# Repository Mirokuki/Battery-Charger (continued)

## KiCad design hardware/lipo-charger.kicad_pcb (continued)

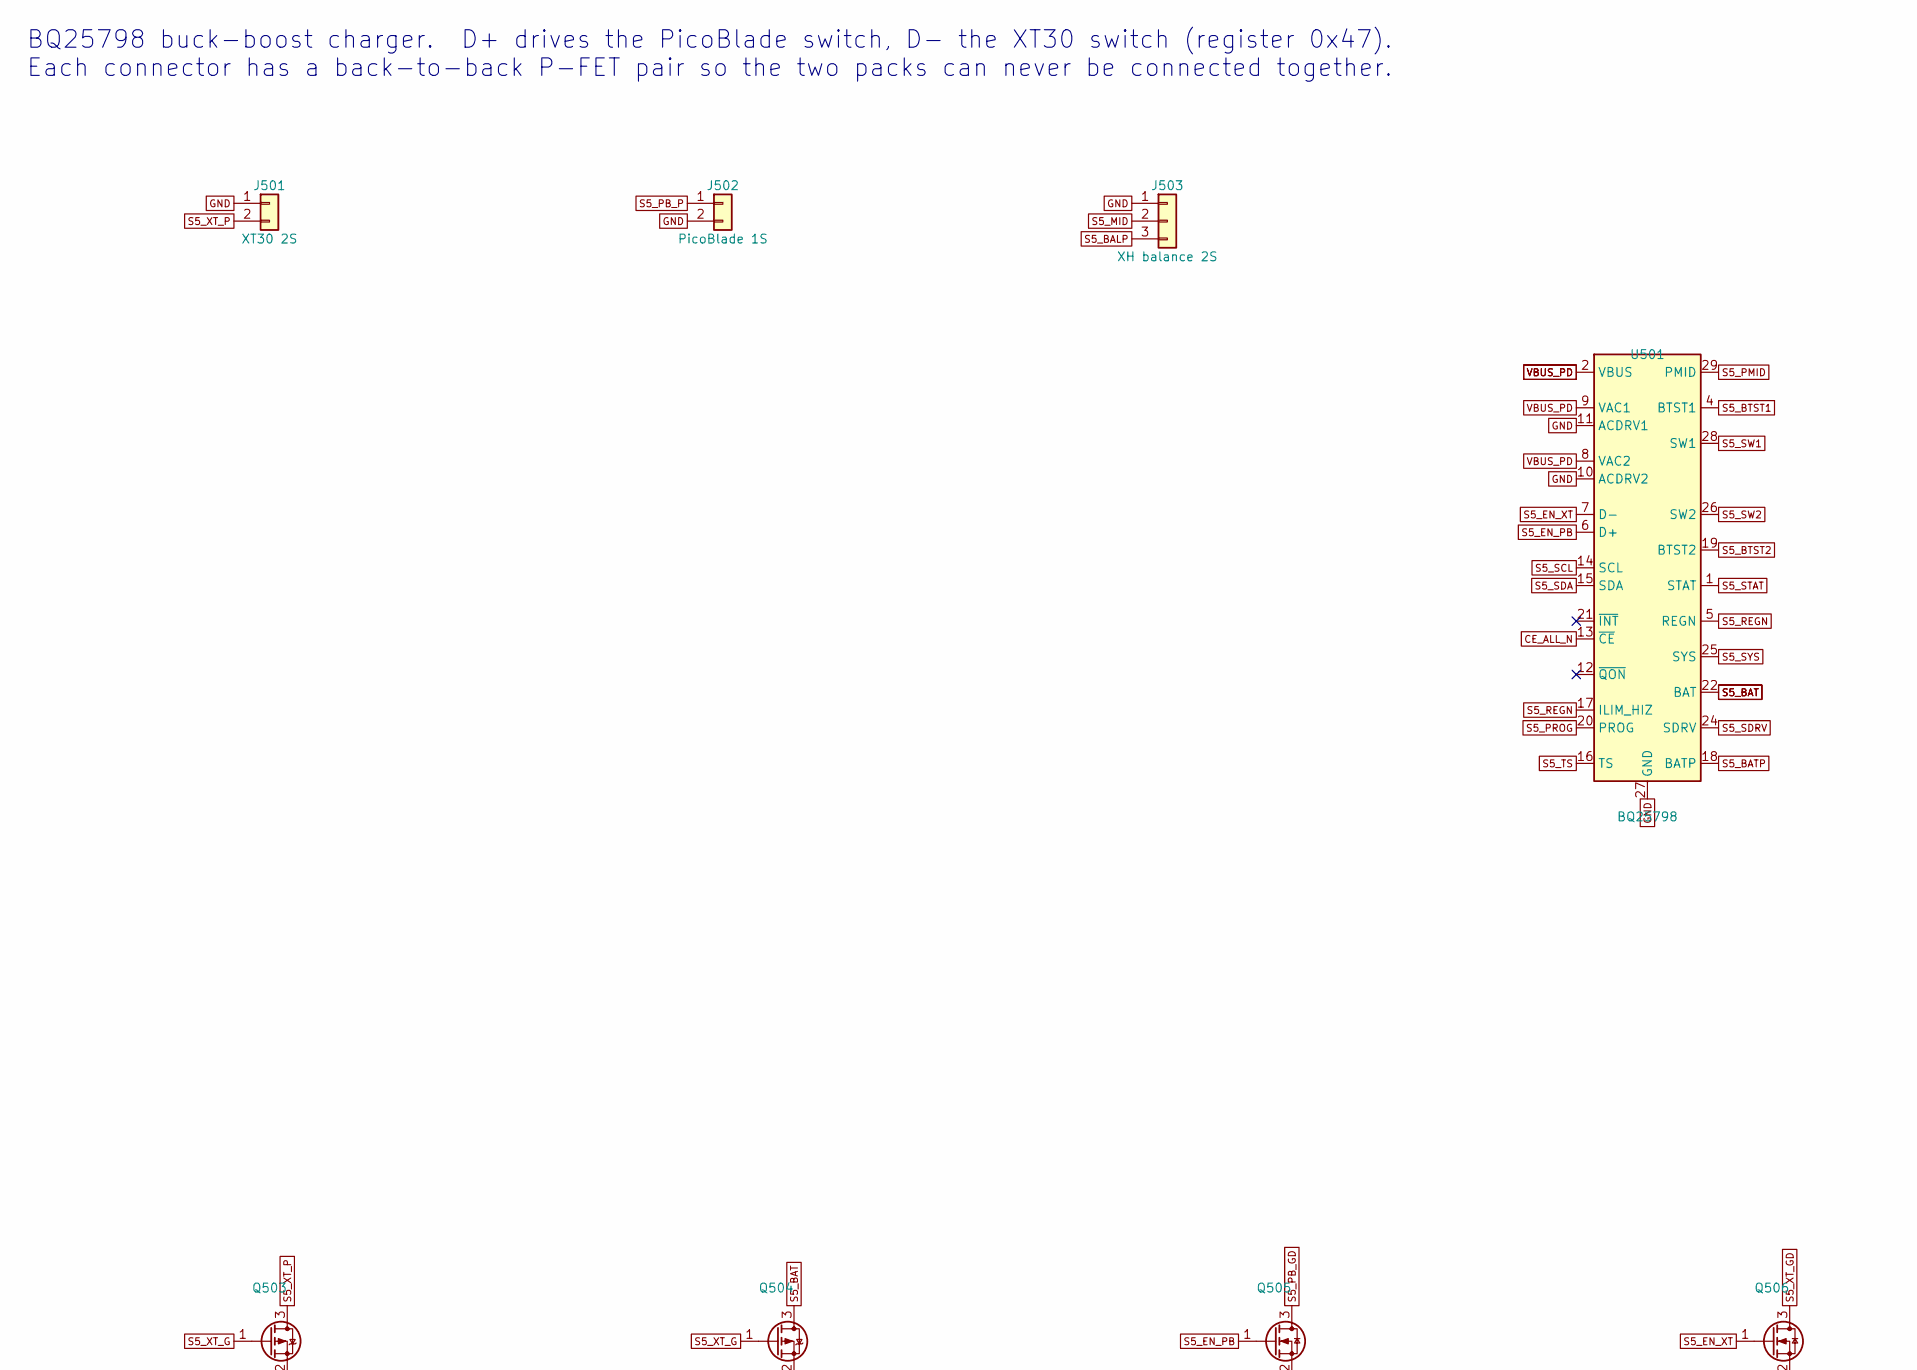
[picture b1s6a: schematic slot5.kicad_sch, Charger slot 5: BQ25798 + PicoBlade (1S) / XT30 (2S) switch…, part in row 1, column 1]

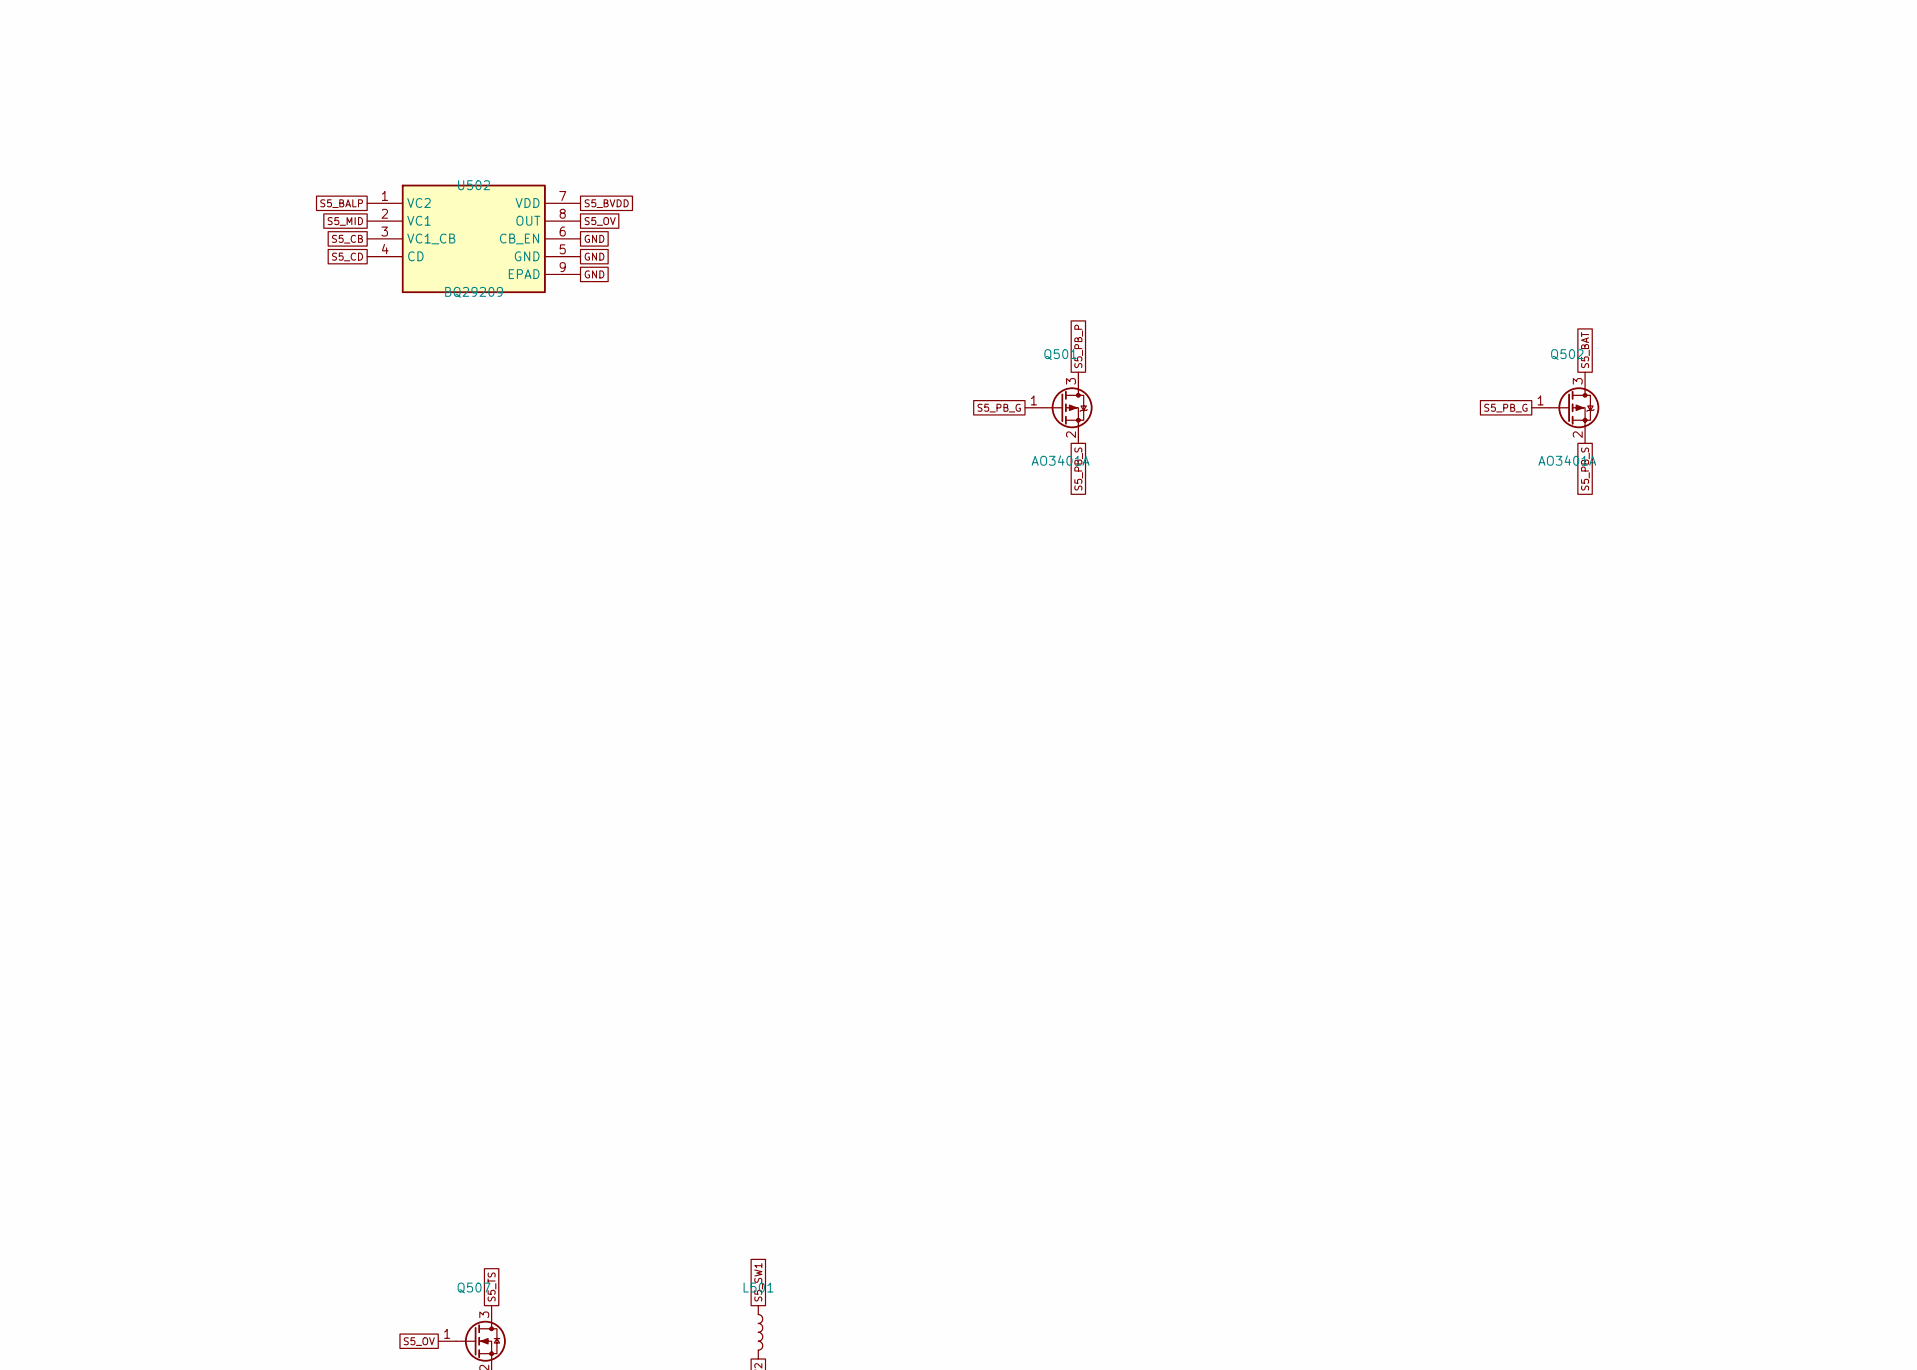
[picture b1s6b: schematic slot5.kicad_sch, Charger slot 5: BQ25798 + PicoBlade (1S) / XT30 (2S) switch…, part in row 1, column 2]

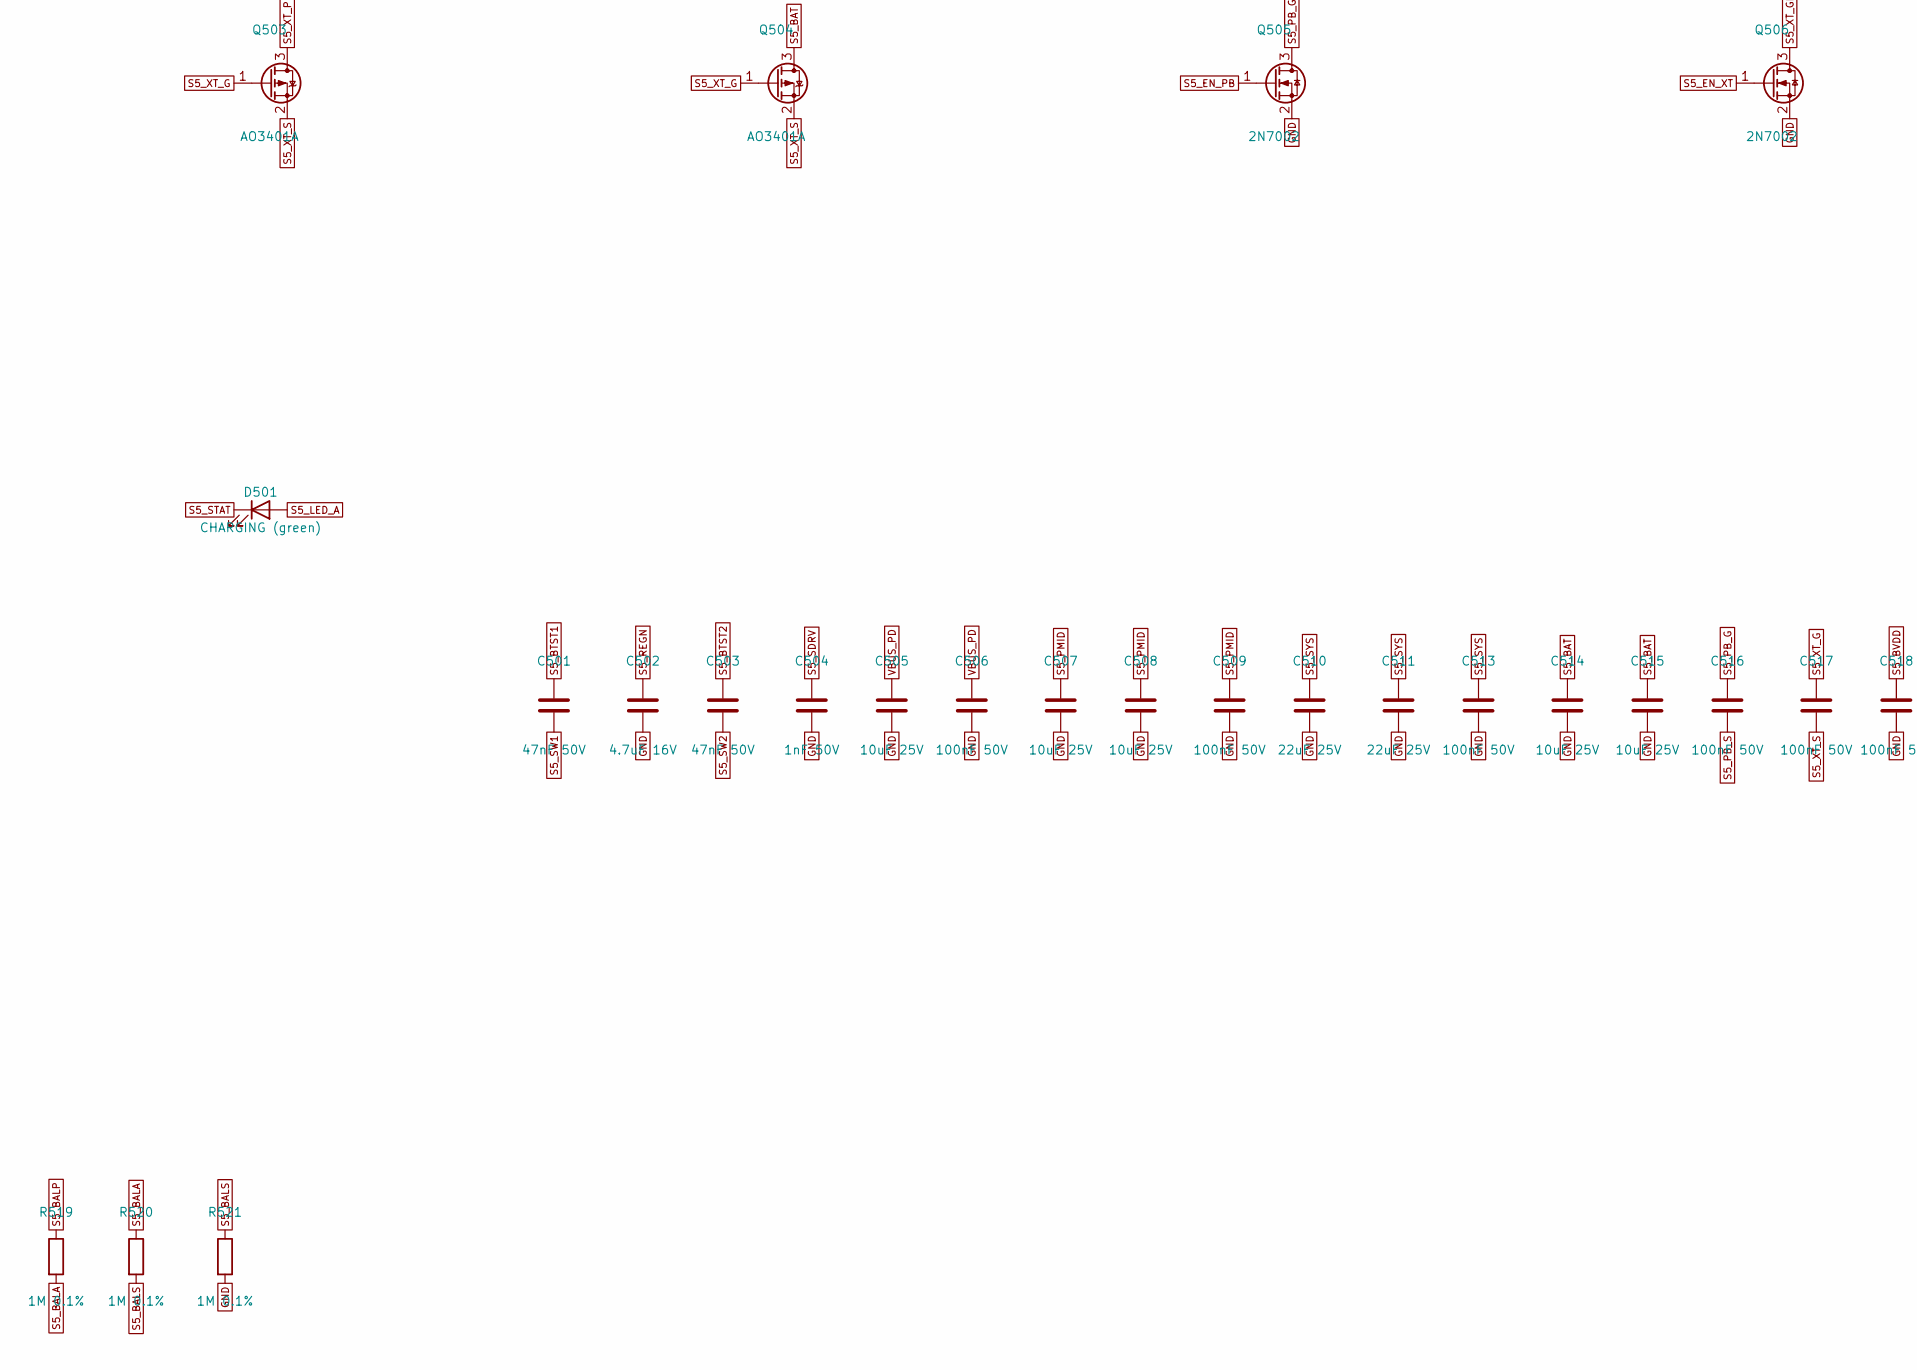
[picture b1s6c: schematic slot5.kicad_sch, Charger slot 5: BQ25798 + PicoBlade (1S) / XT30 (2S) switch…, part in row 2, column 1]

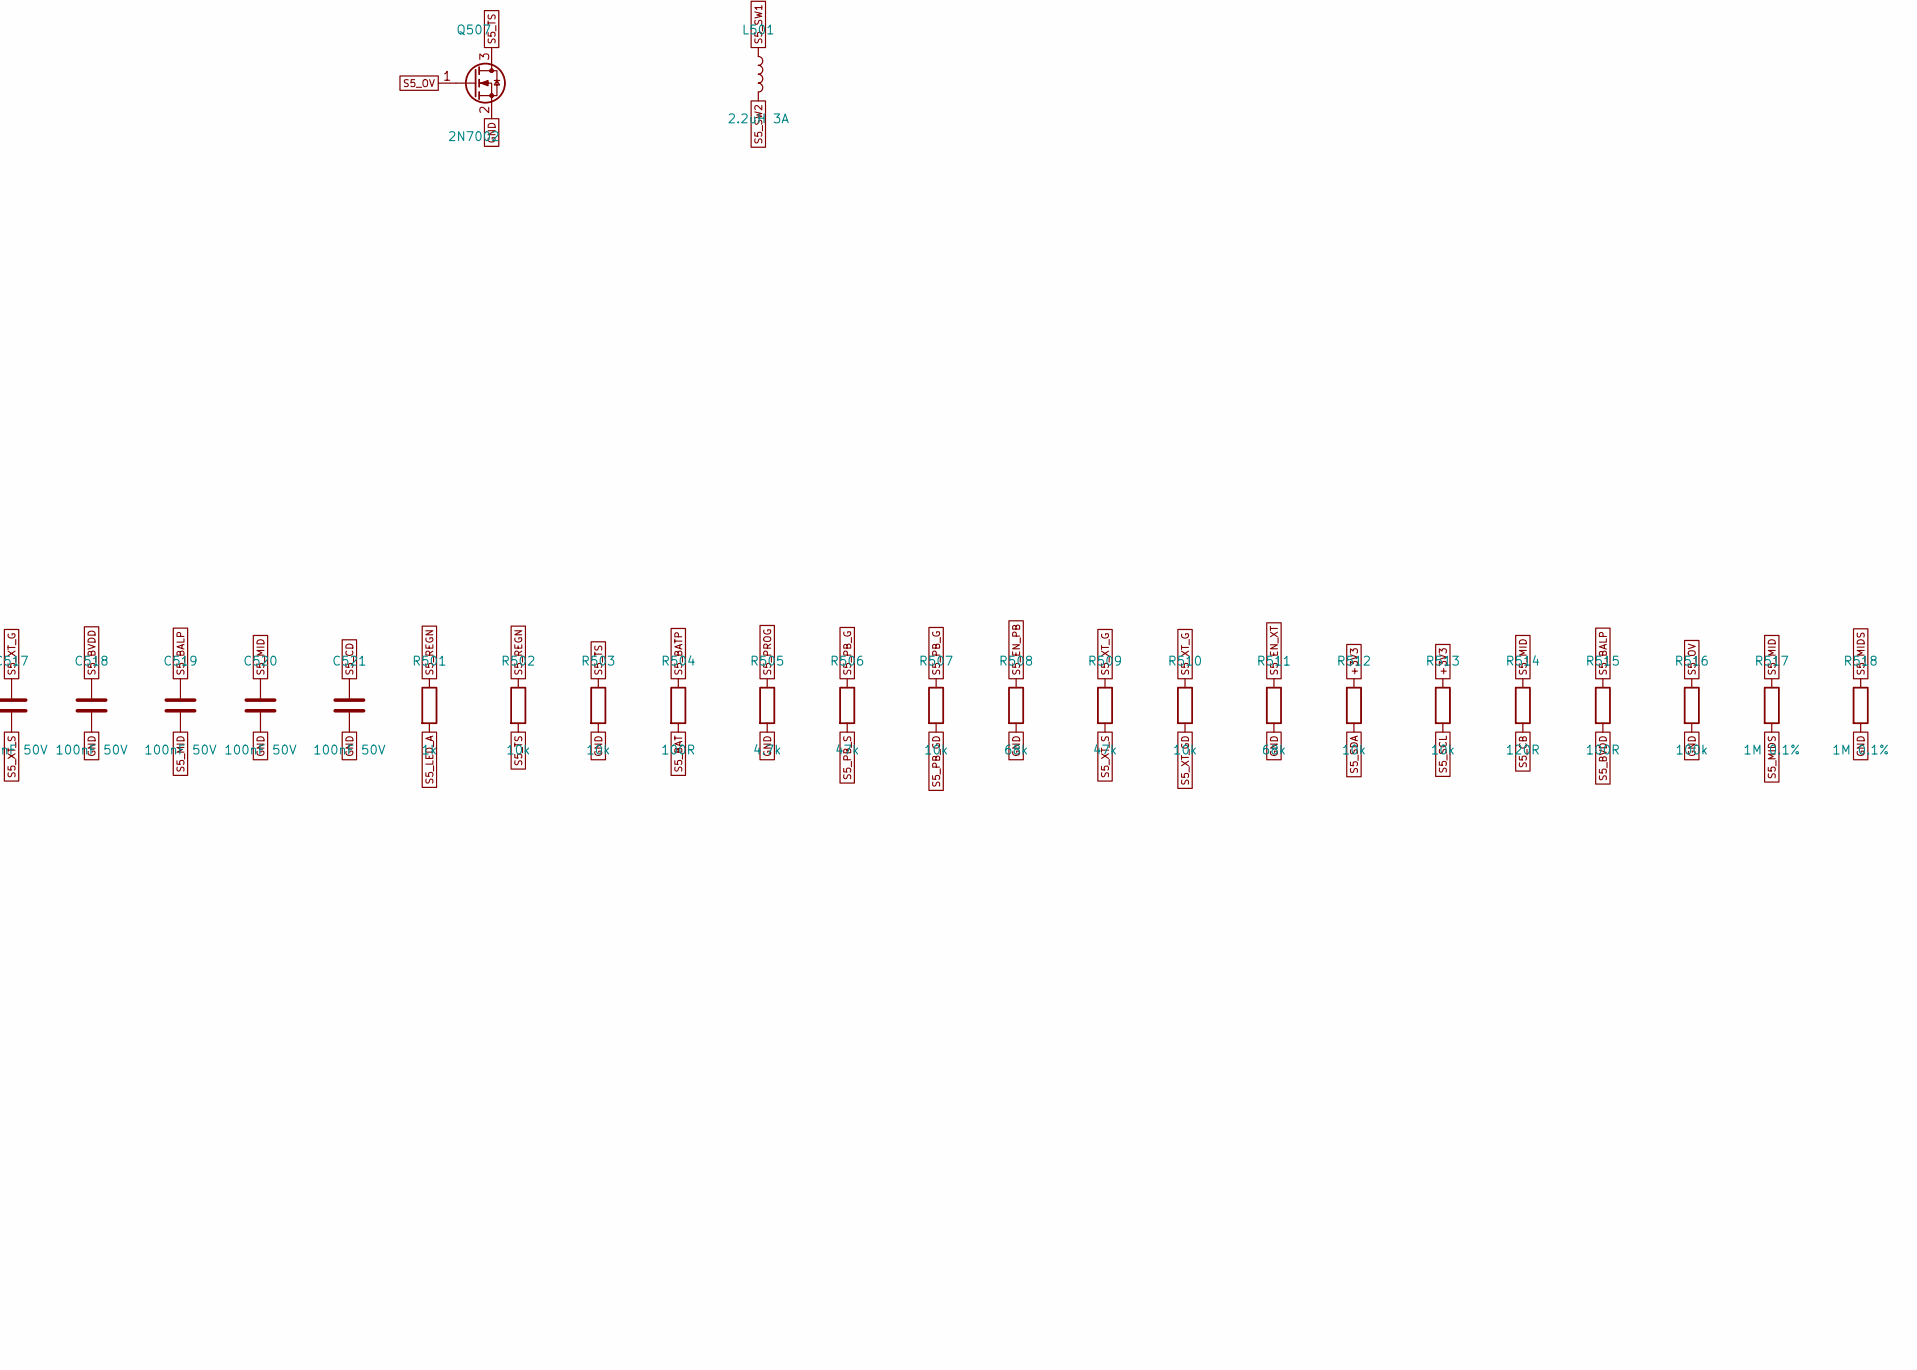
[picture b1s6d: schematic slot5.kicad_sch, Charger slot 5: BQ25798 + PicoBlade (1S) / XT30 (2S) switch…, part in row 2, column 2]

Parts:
C501, C503: 47nF 50V; C_0402_1005Metric; MPN CL05B473KB5NNNC
C502: 4.7uF 16V; C_0603_1608Metric; MPN CL10A475KO8NNNC; LCSC C19666
C504: 1nF 50V; C_0402_1005Metric; MPN CL05B102KB5NNNC; LCSC C1523
C505, C507, C508, C514, C515: 10uF 25V; C_0805_2012Metric; MPN CL21A106KAYNNNE; LCSC C15850
C506, C509, C513, C516, C517, C518, C519, C520, C521: 100nF 50V; C_0402_1005Metric; MPN CL05B104KB54PNC; LCSC C307331
C510, C511: 22uF 25V; C_0805_2012Metric; MPN CL21A226MAQNNNE; LCSC C45783
D501: CHARGING (green); LED_0603_1608Metric; MPN 19-217/GHC-YR1S2/3T; LCSC C72043
J501: XT30 2S; AMASS_XT30UPB-M_1x02_P5.0mm_Vertical; MPN XT30UPB-M; LCSC C99101
J502: PicoBlade 1S; Molex_PicoBlade_53047-0210_1x02_P1.25mm_Vertical; MPN 0530470210
J503: XH balance 2S; JST_XH_B3B-XH-A_1x03_P2.50mm_Vertical; MPN B3B-XH-A; LCSC C144394
L501: 2.2uH 3A; L_Changjiang_FNR4030S; MPN FNR4030S2R2MT
Q501, Q502, Q503, Q504: AO3401A; SOT-23; MPN AO3401A; LCSC C15127
Q505, Q506, Q507: 2N7002; SOT-23; MPN 2N7002; LCSC C8545
R501: 1k; R_0402_1005Metric; MPN 0402WGF1001TCE; LCSC C11702
R502, R503, R507, R510, R512, R513: 10k; R_0402_1005Metric; MPN 0402WGF1002TCE; LCSC C25744
R504, R515: 100R; R_0402_1005Metric; MPN 0402WGF1000TCE; LCSC C25076
R505: 4.7k; R_0402_1005Metric; MPN 0402WGF4701TCE; LCSC C25900
R506, R509: 47k; R_0402_1005Metric; MPN 0402WGF4702TCE; LCSC C25792
R508, R511: 68k; R_0402_1005Metric; MPN 0402WGF6802TCE; LCSC C36871
R514: 120R; R_0402_1005Metric; MPN 0402WGF1200TCE
R516: 100k; R_0402_1005Metric; MPN 0402WGF1003TCE; LCSC C25741
R517, R518, R519, R520, R521: 1M 0.1%; R_0402_1005Metric; MPN RT0402BRD071ML
U501: BQ25798; Texas_RQM0029A_VQFN-29_4x4mm_P0.4mm; MPN BQ25798RQMR; LCSC C2876768
U502: BQ29209; VSON-8-1EP_3x3mm_P0.65mm_EP1.65x2.4mm; MPN BQ29209DRBR

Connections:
+3V3: R512.1, R513.1; also elsewhere on the board
CE_ALL_N: U501.13 (~CE); also elsewhere on the board
GND: C502.2, C504.2, C505.2, C506.2, C507.2, C508.2, C509.2, C510.2, C511.2, C513.2, C514.2, C515.2, C518.2, C520.2, C521.2, J501.1, J502.2, J503.1, Q505.2 (S), Q506.2 (S), Q507.2 (S), R503.2, R505.2, R508.2, R511.2, R516.2, R518.2, R521.2, U501.10 (ACDRV2), U501.11 (ACDRV1), U501.27 (GND), U502.5 (GND), U502.6 (CB_EN), U502.9 (EPAD); also elsewhere on the board
S5_BALA: R519.2, R520.1
S5_BALP: C519.1, J503.3, R515.1, R519.1, U502.1 (VC2)
S5_BALS: R520.2, R521.1; also elsewhere on the board
S5_BAT: C514.1, C515.1, Q502.3 (D), Q504.3 (D), R504.2, U501.22 (BAT), U501.23 (BAT)
S5_BATP: R504.1, U501.18 (BATP)
S5_BTST1: C501.1, U501.4 (BTST1)
S5_BTST2: C503.1, U501.19 (BTST2)
S5_BVDD: C518.1, R515.2, U502.7 (VDD)
S5_CB: R514.2, U502.3 (VC1_CB)
S5_CD: C521.1, U502.4 (CD)
S5_EN_PB: Q505.1 (G), R508.1, U501.6 (D+)
S5_EN_XT: Q506.1 (G), R511.1, U501.7 (D-)
S5_LED_A: D501.2 (A), R501.2
S5_MID: C519.2, C520.1, J503.2, R514.1, R517.1, U502.2 (VC1)
S5_MIDS: R517.2, R518.1; also elsewhere on the board
S5_OV: Q507.1 (G), R516.1, U502.8 (OUT)
S5_PB_G: C516.1, Q501.1 (G), Q502.1 (G), R506.1, R507.1
S5_PB_GD: Q505.3 (D), R507.2
S5_PB_P: J502.1, Q501.3 (D)
S5_PB_S: C516.2, Q501.2 (S), Q502.2 (S), R506.2
S5_PMID: C507.1, C508.1, C509.1, U501.29 (PMID)
S5_PROG: R505.1, U501.20 (PROG)
S5_REGN: C502.1, R501.1, R502.1, U501.5 (REGN), U501.17 (ILIM_HIZ)
S5_SCL: R513.2, U501.14 (SCL); also elsewhere on the board
S5_SDA: R512.2, U501.15 (SDA); also elsewhere on the board
S5_SDRV: C504.1, U501.24 (SDRV)
S5_STAT: D501.1 (K), U501.1 (STAT)
S5_SW1: C501.2, L501.1, U501.28 (SW1)
S5_SW2: C503.2, L501.2, U501.26 (SW2)
S5_SYS: C510.1, C511.1, C513.1, U501.25 (SYS)
S5_TS: Q507.3 (D), R502.2, R503.1, U501.16 (TS)
S5_XT_G: C517.1, Q503.1 (G), Q504.1 (G), R509.1, R510.1
S5_XT_GD: Q506.3 (D), R510.2
S5_XT_P: J501.2, Q503.3 (D)
S5_XT_S: C517.2, Q503.2 (S), Q504.2 (S), R509.2
VBUS_PD: C505.1, C506.1, U501.2 (VBUS), U501.3 (VBUS), U501.8 (VAC2), U501.9 (VAC1); also elsewhere on the board

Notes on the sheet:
BQ25798 buck-boost charger. D+ drives the PicoBlade switch, D- the XT30 switch (register 0x47). Each connector has a back-to-back P-FET pair so the two packs can never be connected together.
